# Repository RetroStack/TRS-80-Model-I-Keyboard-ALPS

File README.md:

# TRS-80 Model 1 - ALPS Keyboard Replica PCB

This project is a faithful reimplementation of the ALPS keyboard PCB of the iconic TRS-80 Model 1 computer. My revision, the E1, is designed to replicate the PCB design 1-to-1 of the original down to the traces. The entire project is available under the MIT license.

## Project Details

### Latest Files

In the "Latest" folder, you'll find the most up-to-date design files, including:

- Gerber files suitable for popular online PCB manufacturers like [PCBWay](/Latest/TRS80_Model_I_Keyboard_ALPS_E1_Gerber_PCBWay.zip) and [JLCPCB](/Latest/TRS80_Model_I_Keyboard_ALPS_E1_Gerber_JLCPCB.zip). Most manufacturers should be fine with either.
- A Bill of Materials (BOM) in [PDF](/Latest/TRS80_Model_I_Keyboard_ALPS_E1_BOM.pdf) format.
- The [full schematics](/Latest/TRS80_Model_I_Keyboard_ALPS_E1_Schematics.pdf) of the E1 replica which is 1:1 to the original G board.

### Implementation

E1 has been implemented using KiCAD 7. The KiCAD project files are included in this repository.

### RetroStack Libraries

To work with this KiCAD project, you'll need the RetroStack libraries for KiCAD. Please [follow this link](https://www.github.com/RetroStack/KiCAD-Libraries) to access and install these libraries.

## Main TRS-80 Model 1 Repository

For additional resources related to the TRS-80 Model 1, be sure to check out the [central page for the TRS-80 Model 1](https://www.github.com/RetroStack/TRS-80-Model-I) on [RetroStack](https://www.github.com/RetroStack).

## Support this Project

RetroStack is passionate about exploring and preserving the legacy of older computer systems. My work involves creating detailed documentation and videos to share the knowledge. I am also dedicated to reviving these classic systems by reimplementing them and offering replacement parts at no cost. If you're keen on supporting this unique project, I invite you to visit my [Patreon page](https://www.patreon.com/RetroStack). Your support would be immensely valuable and greatly appreciated!

## License

This project is licensed under the MIT License - see the [LICENSE](LICENSE) file for details.

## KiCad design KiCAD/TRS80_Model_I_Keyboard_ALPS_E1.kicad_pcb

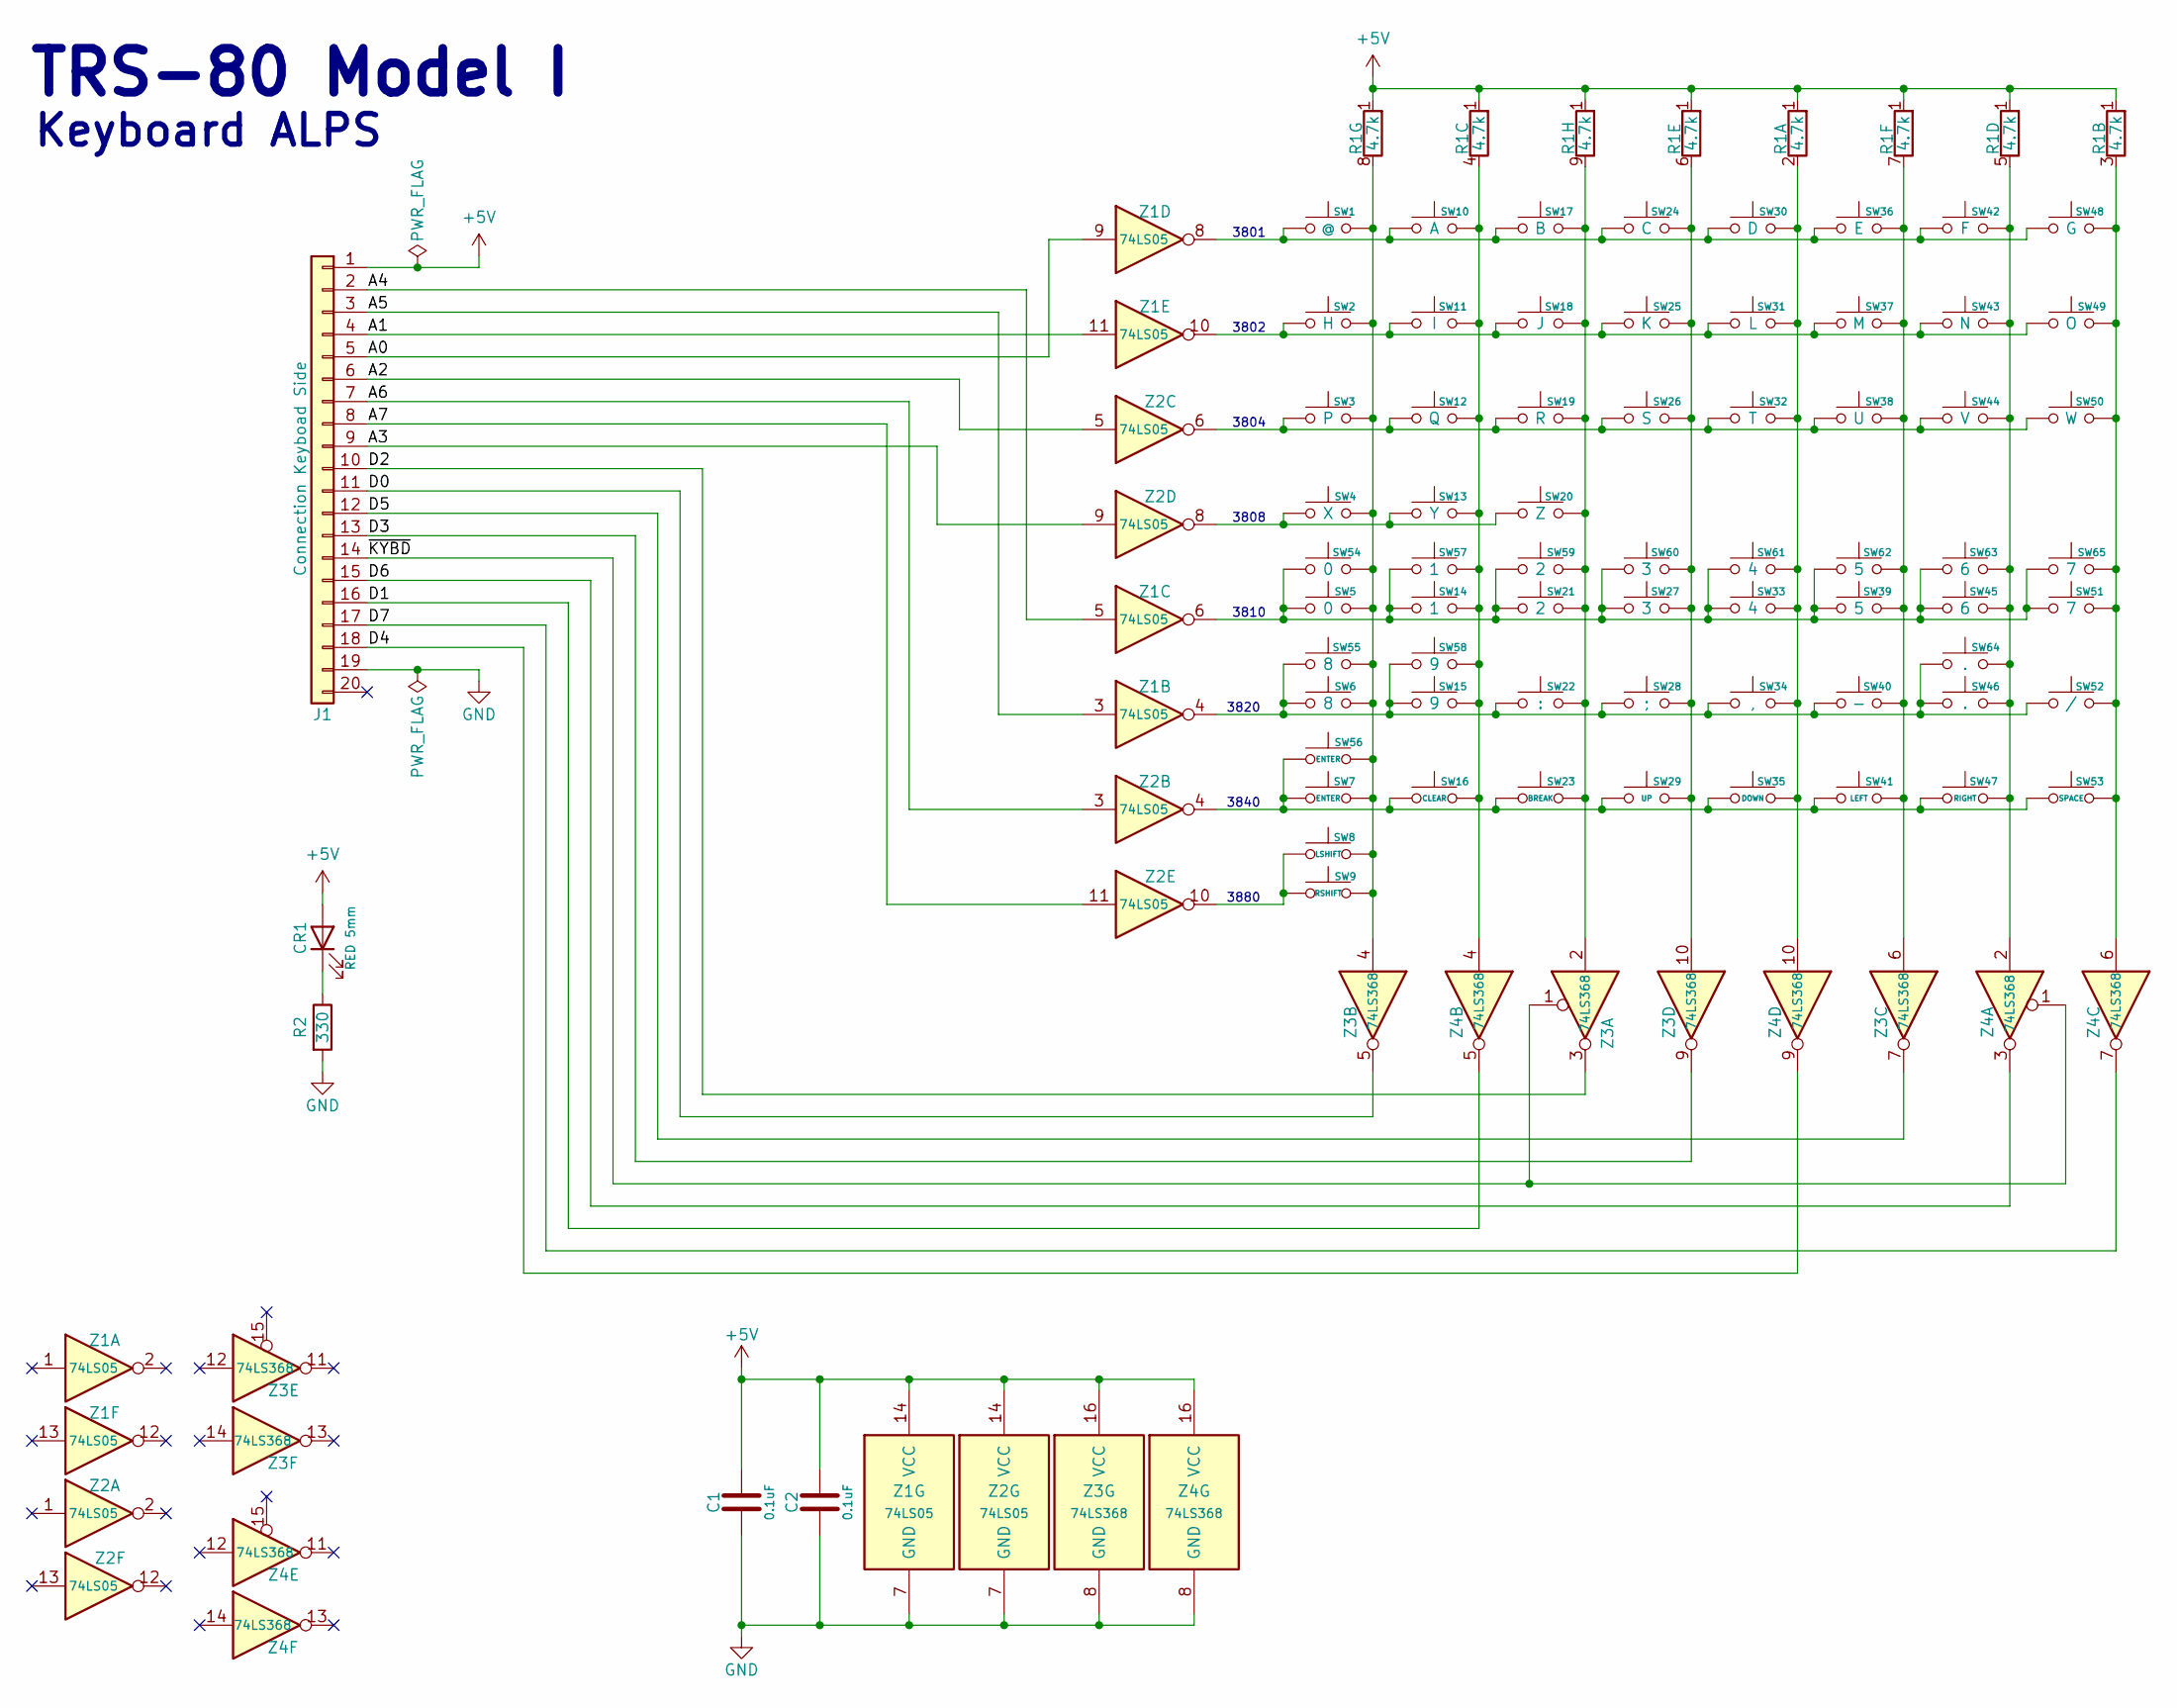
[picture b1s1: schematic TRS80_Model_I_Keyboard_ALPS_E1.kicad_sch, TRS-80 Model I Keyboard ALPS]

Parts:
C1, C2: 0.1uF; TRS80_Model_I_C_Disc_9.5L_4W_6P_Small
CR1: RED 5mm; LED_D5.0mm
J1: Connection Keyboad Side; PinHeader_1x20_P2.54mm_Vertical
R1: 4.7k; R_Array_SIP9
R2: 330; TRS80_Model_I_R_0.25W
SW1: @; SW_Matias_1.00u
SW2: H; SW_Matias_1.00u
SW3: P; SW_Matias_1.00u
SW4: X; SW_Matias_1.00u
SW5, SW54: 0; SW_Matias_1.00u
SW6, SW55: 8; SW_Matias_1.00u
SW7, SW56: ENTER; SW_Matias_1.00u
SW8: LSHIFT; SW_Matias_1.00u
SW9: RSHIFT; SW_Matias_1.00u
SW10: A; SW_Matias_1.00u
SW11: I; SW_Matias_1.00u
SW12: Q; SW_Matias_1.00u
SW13: Y; SW_Matias_1.00u
SW14, SW57: 1; SW_Matias_1.00u
SW15, SW58: 9; SW_Matias_1.00u
SW16: CLEAR; SW_Matias_1.00u
SW17: B; SW_Matias_1.00u
SW18: J; SW_Matias_1.00u
SW19: R; SW_Matias_1.00u
SW20: Z; SW_Matias_1.00u
SW21, SW59: 2; SW_Matias_1.00u
SW22: :; SW_Matias_1.00u
SW23: BREAK; SW_Matias_1.00u
SW24: C; SW_Matias_1.00u
SW25: K; SW_Matias_1.00u
SW26: S; SW_Matias_1.00u
SW27, SW60: 3; SW_Matias_1.00u
SW28: ;; SW_Matias_1.00u
SW29: UP; SW_Matias_1.00u
SW30: D; SW_Matias_1.00u
SW31: L; SW_Matias_1.00u
SW32: T; SW_Matias_1.00u
SW33, SW61: 4; SW_Matias_1.00u
SW34: ,; SW_Matias_1.00u
SW35: DOWN; SW_Matias_1.00u
SW36: E; SW_Matias_1.00u
SW37: M; SW_Matias_1.00u
SW38: U; SW_Matias_1.00u
SW39, SW62: 5; SW_Matias_1.00u
SW40: -; SW_Matias_1.00u
SW41: LEFT; SW_Matias_1.00u
SW42: F; SW_Matias_1.00u
SW43: N; SW_Matias_1.00u
SW44: V; SW_Matias_1.00u
SW45, SW63: 6; SW_Matias_1.00u
SW46, SW64: .; SW_Matias_1.00u
SW47: RIGHT; SW_Matias_1.00u
SW48: G; SW_Matias_1.00u
SW49: O; SW_Matias_1.00u
SW50: W; SW_Matias_1.00u
SW51, SW65: 7; SW_Matias_1.00u
SW52: /; SW_Matias_1.00u
SW53: SPACE; SW_Matias_1.00u
Z1, Z2: 74LS05; TRS80_Model_I_DIP14
Z3, Z4: 74LS368; TRS80_Model_I_DIP16

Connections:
+5V: C1.1, C2.1, CR1.2 (A), J1.1, R1.1 (R1), Z1.14 (VCC), Z2.14 (VCC), Z3.16 (VCC), Z4.16 (VCC)
/A0: J1.5, Z1.9
/A1: J1.4, Z1.11
/A2: J1.6, Z2.5
/A3: J1.9, Z2.9
/A4: J1.2, Z1.5
/A5: J1.3, Z1.3
/A6: J1.7, Z2.3
/A7: J1.8, Z2.11
/D0: J1.11, Z3.5
/D1: J1.16, Z4.5
/D2: J1.10, Z3.3
/D3: J1.13, Z3.9
/D4: J1.18, Z4.9
/D5: J1.12, Z3.7
/D6: J1.15, Z4.3
/D7: J1.17, Z4.7
/~KYBD: J1.14, Z3.1, Z4.1
GND: C1.2, C2.2, J1.19, R2.2, Z1.7 (GND), Z2.7 (GND), Z3.8 (GND), Z4.8 (GND)
unnamed: CR1.1 (K), R2.1
unnamed: R1.2 (R1.2), SW30.2, SW31.1, SW32.2, SW33.1, SW34.2, SW35.1, SW61.1, Z4.10
unnamed: R1.3 (R2.2), SW48.1, SW49.2, SW50.1, SW51.1, SW52.1, SW53.1, SW65.2, Z4.6
unnamed: R1.4 (R3.2), SW10.2, SW11.1, SW12.1, SW13.1, SW14.1, SW15.1, SW16.2, SW57.1, SW58.1, Z4.4
unnamed: R1.5 (R4.2), SW42.2, SW43.2, SW44.2, SW45.1, SW46.2, SW47.1, SW63.1, SW64.2, Z4.2
unnamed: R1.6 (R5.2), SW24.1, SW25.2, SW26.2, SW27.1, SW28.2, SW29.2, SW60.1, Z3.10
unnamed: R1.7 (R6.2), SW36.2, SW37.2, SW38.2, SW39.1, SW40.1, SW41.2, SW62.1, Z3.6
unnamed: R1.8 (R7.2), SW1.1, SW2.1, SW3.1, SW4.2, SW5.2, SW6.2, SW7.1, SW8.1, SW9.2, SW54.1, SW55.1, SW56.2, Z3.4
unnamed: R1.9 (R8.2), SW17.1, SW18.1, SW19.2, SW20.1, SW21.2, SW22.2, SW23.2, SW59.2, Z3.2
unnamed: SW1.2, SW10.1, SW17.2, SW24.2, SW30.1, SW36.1, SW42.1, SW48.2, Z1.8
unnamed: SW8.2, SW9.1, Z2.10
unnamed: SW2.2, SW11.2, SW18.2, SW25.1, SW31.2, SW37.1, SW43.1, SW49.1, Z1.10
unnamed: SW3.2, SW12.2, SW19.1, SW26.1, SW32.1, SW38.1, SW44.1, SW50.2, Z2.6
unnamed: SW4.1, SW13.2, SW20.2, Z2.8
unnamed: SW5.1, SW14.2, SW21.1, SW27.2, SW33.2, SW39.2, SW45.2, SW51.2, SW54.2, SW57.2, SW59.1, SW60.2, SW61.2, SW62.2, SW63.2, SW65.1, Z1.6
unnamed: SW6.1, SW15.2, SW22.1, SW28.1, SW34.1, SW40.2, SW46.1, SW52.2, SW55.2, SW58.2, SW64.1, Z1.4
unnamed: SW7.2, SW16.1, SW23.1, SW29.1, SW35.2, SW41.1, SW47.2, SW53.2, SW56.1, Z2.4

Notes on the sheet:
3804
3880
TRS-80 Model I
Keyboard ALPS
3808
3810
3820
3802
3801
3840

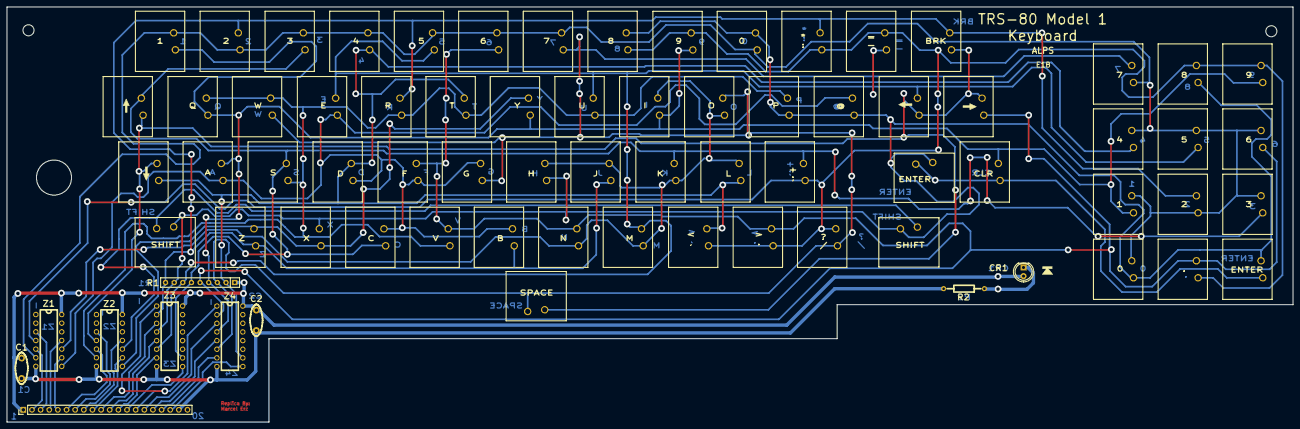
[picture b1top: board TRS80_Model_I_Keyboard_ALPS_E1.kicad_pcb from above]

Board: 2 copper layers, 378.0 x 122.0 mm, 75 parts (0 on the bottom side), 36 nets.

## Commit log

2024-01-14 E1A initial commit
2024-01-22 Update LICENSE
2024-01-22 Cleanup & Front Silkscreen
2024-01-22 Typos
2024-12-21 General Update
